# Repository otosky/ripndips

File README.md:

# Rip N Dips

Adapted Split-Ergo keyboard designs

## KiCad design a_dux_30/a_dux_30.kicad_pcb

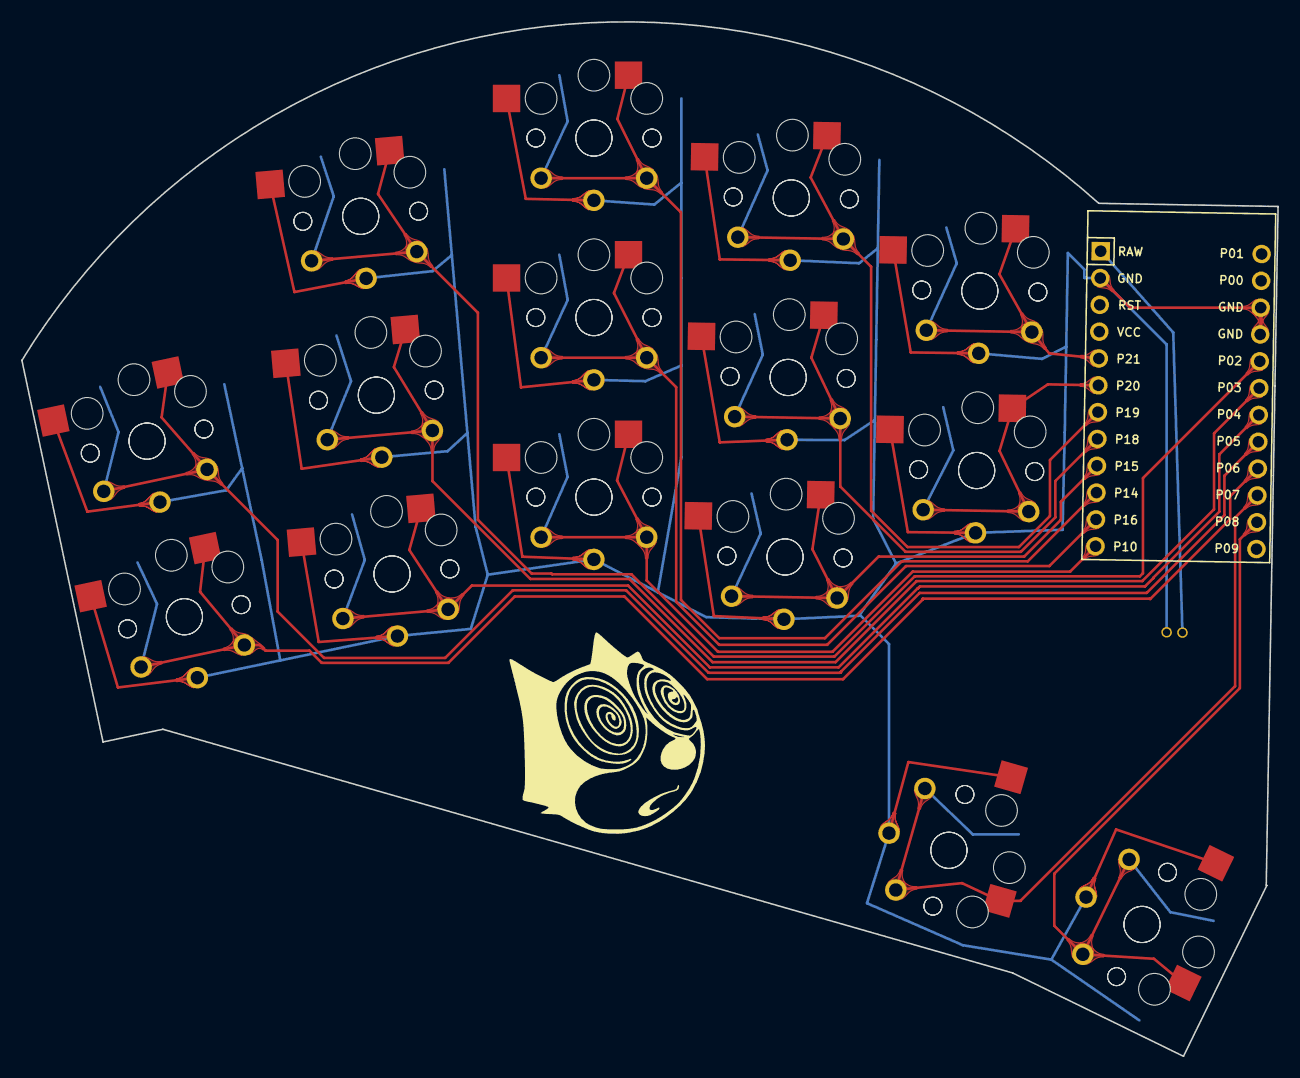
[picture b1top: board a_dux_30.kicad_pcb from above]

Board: 2 copper layers, 118.9 x 97.9 mm, 31 parts (0 on the bottom side), 16 nets.

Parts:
MCU1: ProMicro
S1, S2, S3, S4, S5, S6, S7, S8, S9, S10, S11, S12, S13, S14, S15, S16, S17, S18, S19, S20, S21, S22, S23, S24, S25, S26, S27, S28, S29, S30: PG1350

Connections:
GND: MCU1.2, MCU1.15, MCU1.16, S1.2, S2.2, S3.2, S4.2, S5.2, S6.2, S7.2, S8.2, S9.2, S10.2, S11.2, S12.2, S13.2, S14.2, S15.2, S16.2, S17.2, S18.2, S19.2, S20.2, S21.2, S22.2, S23.2, S24.2, S25.2, S26.2, S27.2, S28.2, S29.2, S30.2
P2: MCU1.17, S9.1, S10.1
P3: MCU1.18, S7.1, S8.1
P4: MCU1.19, S5.1, S6.1
P5: MCU1.20, S3.1, S4.1
P6: MCU1.21, S1.1, S2.1
P7: MCU1.22, S27.1, S28.1
P8: MCU1.23, S29.1, S30.1
P10: MCU1.12, S11.1, S12.1
P14: MCU1.10, S15.1, S16.1
P15: MCU1.9, S17.1, S18.1
P16: MCU1.11, S13.1, S14.1
P18: MCU1.8, S19.1, S20.1
P19: MCU1.7, S21.1, S22.1
P20: MCU1.6, S23.1, S24.1
P21: MCU1.5, S25.1, S26.1

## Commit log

2022-01-18 remove keys & reduce splay
2022-01-18 rotate thumb switches
2022-01-18 wip swept top
2022-01-20 redo outline
2022-01-20 rotate thumbs
2022-01-20 routed pcb
2022-01-20 ignore DS_Store
2022-01-20 fillet tracks
2022-01-21 add silkscreen
2022-01-21 add gerbers
2022-01-21 no need for .gbr files in addition to zipped
2022-01-21 add teardrops
2022-01-21 add drill files
2022-02-06 increase pinky stagger
2022-02-06 reduce middle-index gap
2022-02-06 move thumbs in towards palm
2022-02-06 add version metadata
2022-02-06 remove unused binds
2022-02-06 ignore node
2022-02-06 add alias for ergogen cli
2022-02-06 add author meta
2022-02-06 update pcb
2022-02-07 redo pin layout
2022-02-07 remove corners
2022-02-07 remove thumb extension outline
2022-02-07 add extra bind to cover hotswap pads around thumbs
2022-02-07 redo pin layout for ring column
2022-02-07 move trrs jack below mcu
2022-02-07 compact pin layouts
2022-02-08 add routes
2022-02-08 add art
2022-02-08 add rendered images of rev2
2022-02-08 add sketchy rounding/fillet
2022-02-08 new gerbers
2022-04-23 fix incorrect pin for trrs
2022-06-07 add v1 img
2022-06-07 add Makefile
2022-06-12 A dux 30 rev2 (#2)
    * increase pinky stagger
    * reduce middle-index gap
    * move thumbs in towards palm
    * add version metadata
    * remove unused binds
    * ignore node
2022-06-12 add a setup step to clone ben vallack's ergogen
2022-06-12 add footprints dir
2022-06-12 replace trrs with bat
2022-06-12 fix outline
    The pinky side of the board has some hotswap pads that were cut off in
    the previous version.
2022-06-12 add kicad project files
2022-06-12 add compiled pcb
2022-06-13 add routes and img
2022-06-13 ignore caches
